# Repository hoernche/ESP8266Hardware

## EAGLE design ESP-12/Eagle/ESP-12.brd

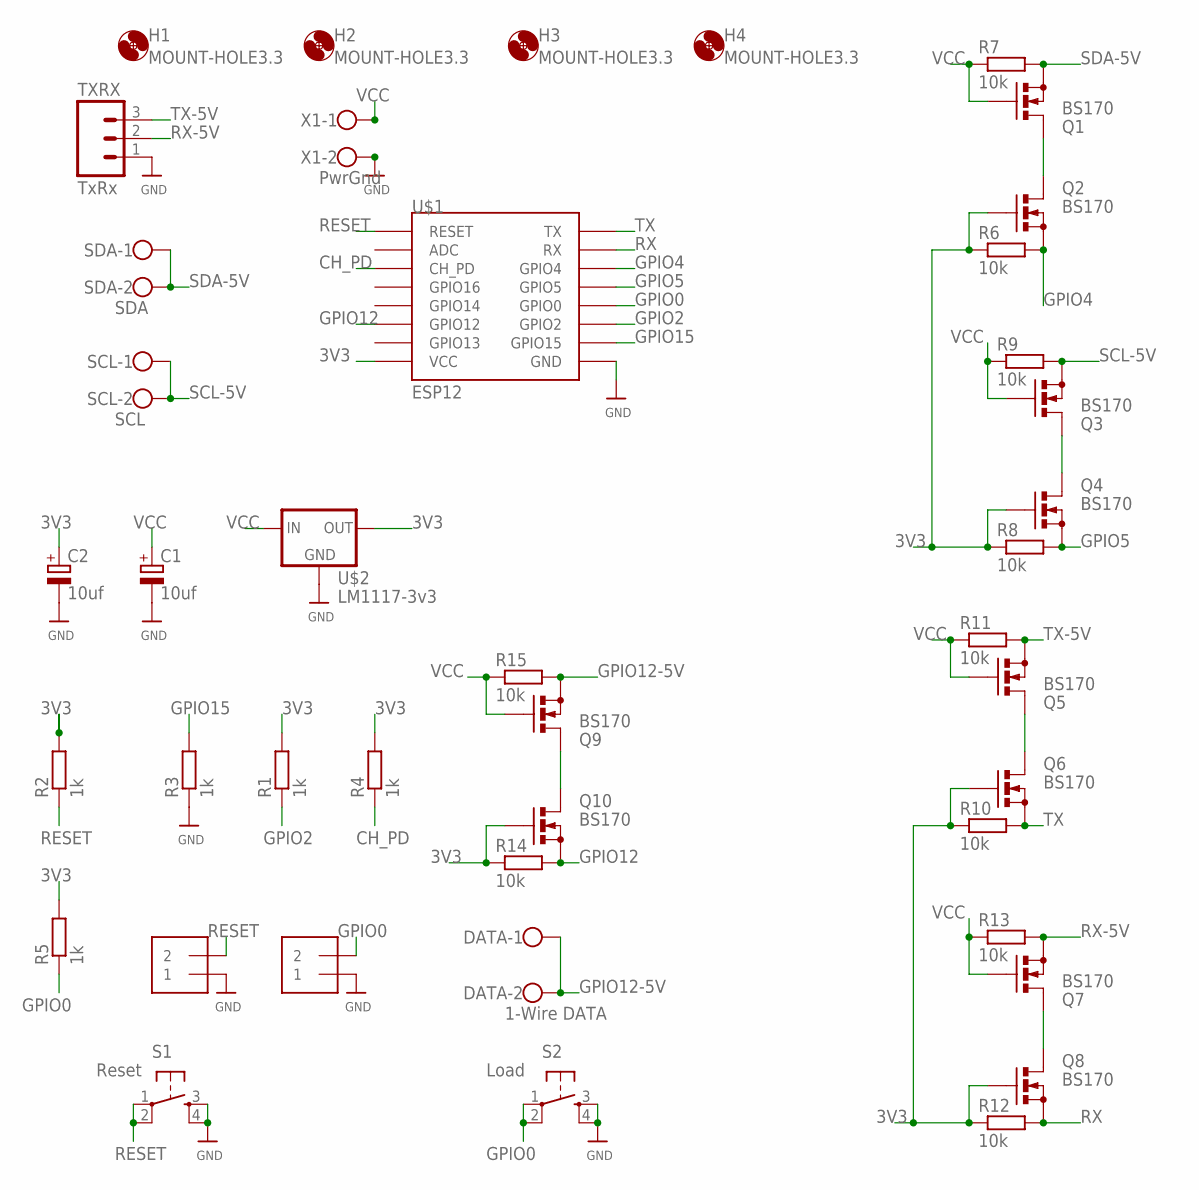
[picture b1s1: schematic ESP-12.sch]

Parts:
C1, C2: 10uf; E5-4
DATA: 1-Wire DATA; W237-102
H1, H2, H3, H4: MOUNT-HOLE3.3; 3,3
J1, J2: 1X2-3.5MM
Q1, Q2, Q3, Q4, Q5, Q6, Q7, Q8, Q9, Q10: BS170; SOT54E
R1, R2, R3, R4, R5: 1k; 0207/10
R6, R7, R8, R9, R10, R11, R12, R13, R14, R15: 10k; 0207/10
S1: Reset; TACTILE-PTH
S2: Load; TACTILE-PTH
SCL: SCL; W237-102
SDA: SDA; W237-102
TXRX: TxRx; 1X03_LONGPADS
U$1: ESP12
U$2: LM1117-3v3; 78XXL
X1: PwrGnd; W237-102

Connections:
3V3: C2.+, Q2.G, Q4.G, Q6.G, Q8.G, Q10.G, R1.2, R2.2, R4.2, R5.2, R6.1, R8.1, R10.1, R12.1, R14.1, U$1.VCC, U$2.GND (OUT)
CH_PD: R4.1, U$1.CH_PD
GND: C1.-, C2.-, J1.1, J2.1, R3.1, S1.3, S1.4, S2.3, S2.4, TXRX.1, U$1.GND, U$2.IN (GND), X1.2
GPIO0: J2.2, R5.1, S2.1, S2.2, U$1.GPIO0
GPIO2: R1.1, U$1.GPIO2
GPIO4: Q2.S, R6.2, U$1.GPIO4
GPIO5: Q4.S, R8.2, U$1.GPIO5
GPIO12: Q10.S, R14.2, U$1.GPIO12
GPIO12-5V: DATA.1, DATA.2, Q9.S, R15.2
GPIO15: R3.2, U$1.GPIO15
unnamed: Q3.D, Q4.D
unnamed: Q1.D, Q2.D
unnamed: Q5.D, Q6.D
unnamed: Q7.D, Q8.D
unnamed: Q9.D, Q10.D
RESET: J1.2, R2.1, S1.1, S1.2, U$1.RESET
RX: Q8.S, R12.2, U$1.RX
RX-5V: Q7.S, R13.2, TXRX.2
SCL-5V: Q3.S, R9.2, SCL.1, SCL.2
SDA-5V: Q1.S, R7.2, SDA.1, SDA.2
TX: Q6.S, R10.2, U$1.TX
TX-5V: Q5.S, R11.2, TXRX.3
VCC: C1.+, Q1.G, Q3.G, Q5.G, Q7.G, Q9.G, R7.1, R9.1, R11.1, R13.1, R15.1, U$2.OUT (IN), X1.1

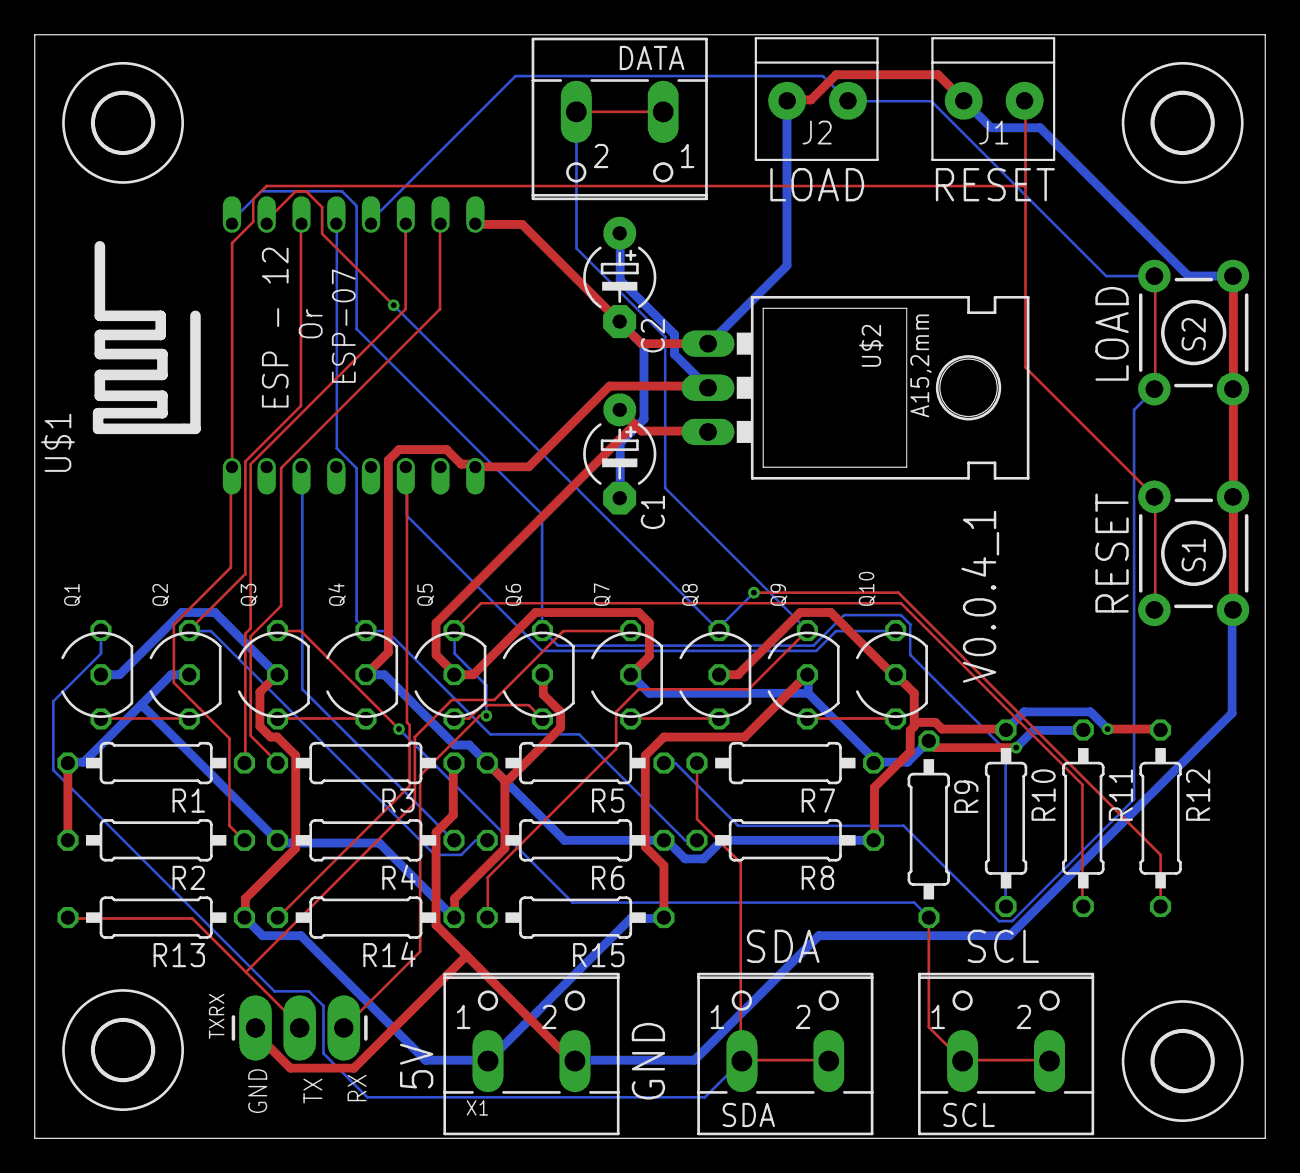
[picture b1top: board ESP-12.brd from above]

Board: 2 copper layers, 70.8 x 63.5 mm, 42 parts (0 on the bottom side), 23 nets.

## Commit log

2015-08-09 ESP-12 V0.0.4

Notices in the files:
parts and their libraries:
SparkFun-PowerIC: Licensing: CC v3.0 Share-Alike You are welcome to use this library for commercial purposes.
microbuilder: This work is placed in the public domain, and may be freely used for commercial and non-commercial work with the following conditions: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
